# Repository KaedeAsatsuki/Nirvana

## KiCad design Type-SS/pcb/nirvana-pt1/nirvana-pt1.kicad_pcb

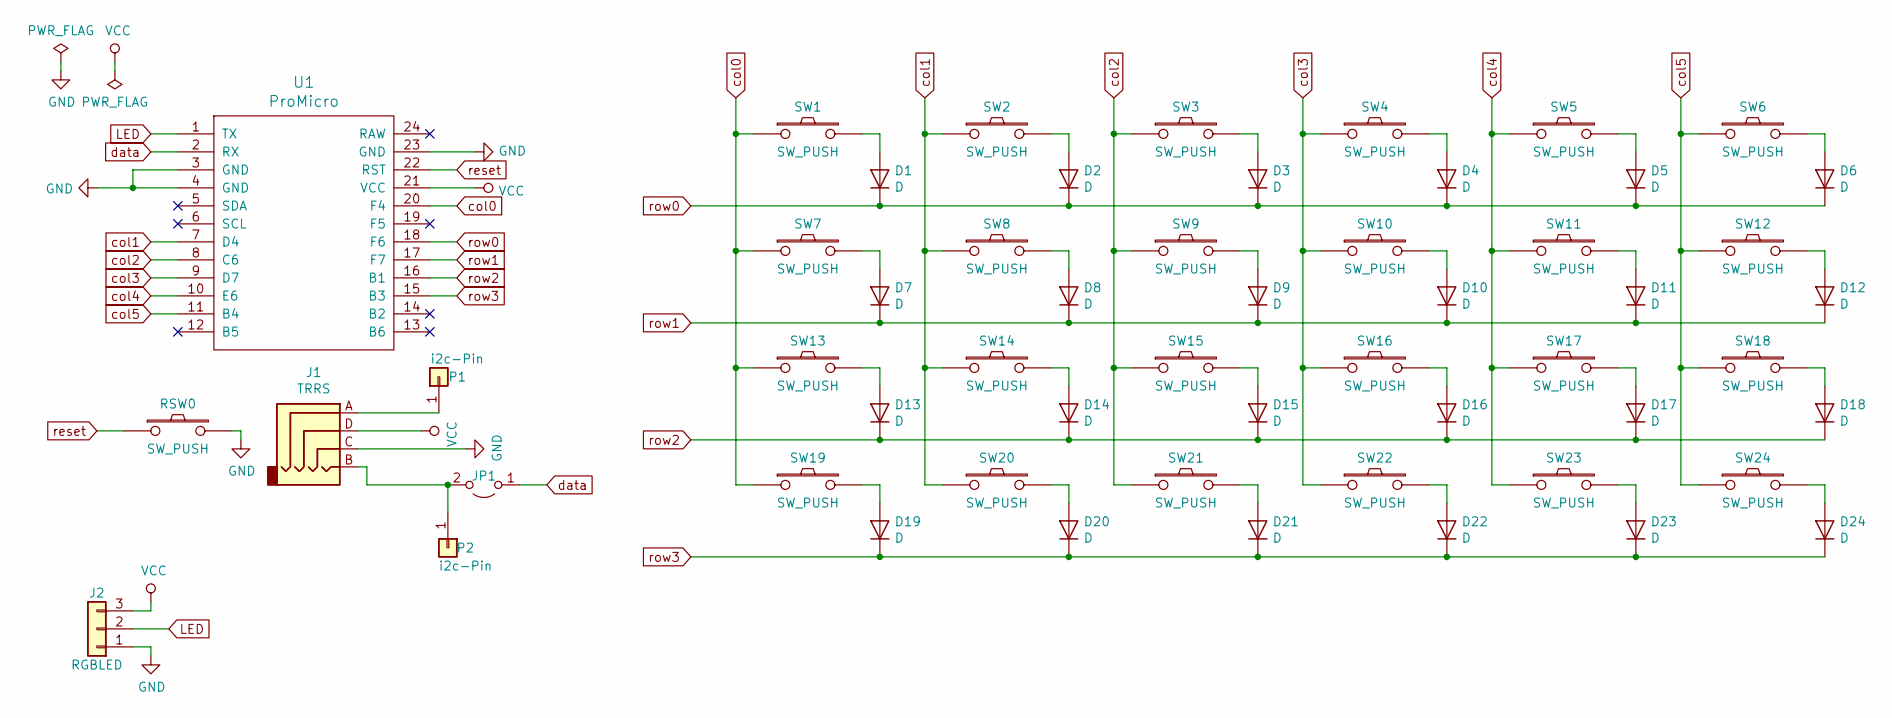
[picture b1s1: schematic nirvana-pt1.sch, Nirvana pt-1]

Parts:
D1, D2, D3, D4, D5, D6, D7, D8, D9, D10, D11, D12, D13, D14, D15, D16, D17, D18, D19, D20, D21, D22, D23, D24: D; D_SMD_re
J1: TRRS; MJ-4PP-9
J2: RGBLED; StripLED_rev
JP1: Jumper_2_Open; SolderJumper-2_P1.3mm_Open_RoundedPad1.0x1.5mm
P1, P2: i2c-Pin; 1pin_conn
RSW0: SW_PUSH; ResetSW
SW1, SW2, SW3, SW4, SW5, SW6, SW7, SW8, SW9, SW10, SW11, SW12, SW13, SW14, SW15, SW16, SW17, SW18, SW21, SW22, SW23, SW24: SW_PUSH; MX_ALPS_PG1350_noLed
SW19, SW20: SW_PUSH; MX_ALPS_PG1350_noLed_1.75u
U1: ProMicro; ProMicro_v2

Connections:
GND: J1.C, J2.1, RSW0.2, U1.3 (GND), U1.4 (GND), U1.23 (GND)
LED: J2.2, U1.1 (TX)
unnamed: D1.2 (A), SW1.2
unnamed: D2.2 (A), SW2.2
unnamed: D3.2 (A), SW3.2
unnamed: D4.2 (A), SW4.2
unnamed: D5.2 (A), SW5.2
unnamed: D6.2 (A), SW6.2
unnamed: D7.2 (A), SW7.2
unnamed: D8.2 (A), SW8.2
unnamed: D9.2 (A), SW9.2
unnamed: D10.2 (A), SW10.2
unnamed: D11.2 (A), SW11.2
unnamed: D12.2 (A), SW12.2
unnamed: D13.2 (A), SW13.2
unnamed: D14.2 (A), SW14.2
unnamed: D15.2 (A), SW15.2
unnamed: D16.2 (A), SW16.2
unnamed: D17.2 (A), SW17.2
unnamed: D18.2 (A), SW18.2
unnamed: D19.2 (A), SW19.2
unnamed: D20.2 (A), SW20.2
unnamed: D21.2 (A), SW21.2
unnamed: D22.2 (A), SW22.2
unnamed: D23.2 (A), SW23.2
unnamed: D24.2 (A), SW24.2
unnamed: J1.A, P1.1
unnamed: J1.B, JP1.2 (B), P2.1
VCC: J1.D, J2.3, U1.21 (VCC)
col0: SW1.1, SW7.1, SW13.1, SW19.1, U1.20 (F4)
col1: SW2.1, SW8.1, SW14.1, SW20.1, U1.7 (D4)
col2: SW3.1, SW9.1, SW15.1, SW21.1, U1.8 (C6)
col3: SW4.1, SW10.1, SW16.1, SW22.1, U1.9 (D7)
col4: SW5.1, SW11.1, SW17.1, SW23.1, U1.10 (E6)
col5: SW6.1, SW12.1, SW18.1, SW24.1, U1.11 (B4)
data: JP1.1 (A), U1.2 (RX)
reset: RSW0.1, U1.22 (RST)
row0: D1.1 (K), D2.1 (K), D3.1 (K), D4.1 (K), D5.1 (K), D6.1 (K), U1.18 (F6)
row1: D7.1 (K), D8.1 (K), D9.1 (K), D10.1 (K), D11.1 (K), D12.1 (K), U1.17 (F7)
row2: D13.1 (K), D14.1 (K), D15.1 (K), D16.1 (K), D17.1 (K), D18.1 (K), U1.16 (B1)
row3: D19.1 (K), D20.1 (K), D21.1 (K), D22.1 (K), D23.1 (K), D24.1 (K), U1.15 (B3)

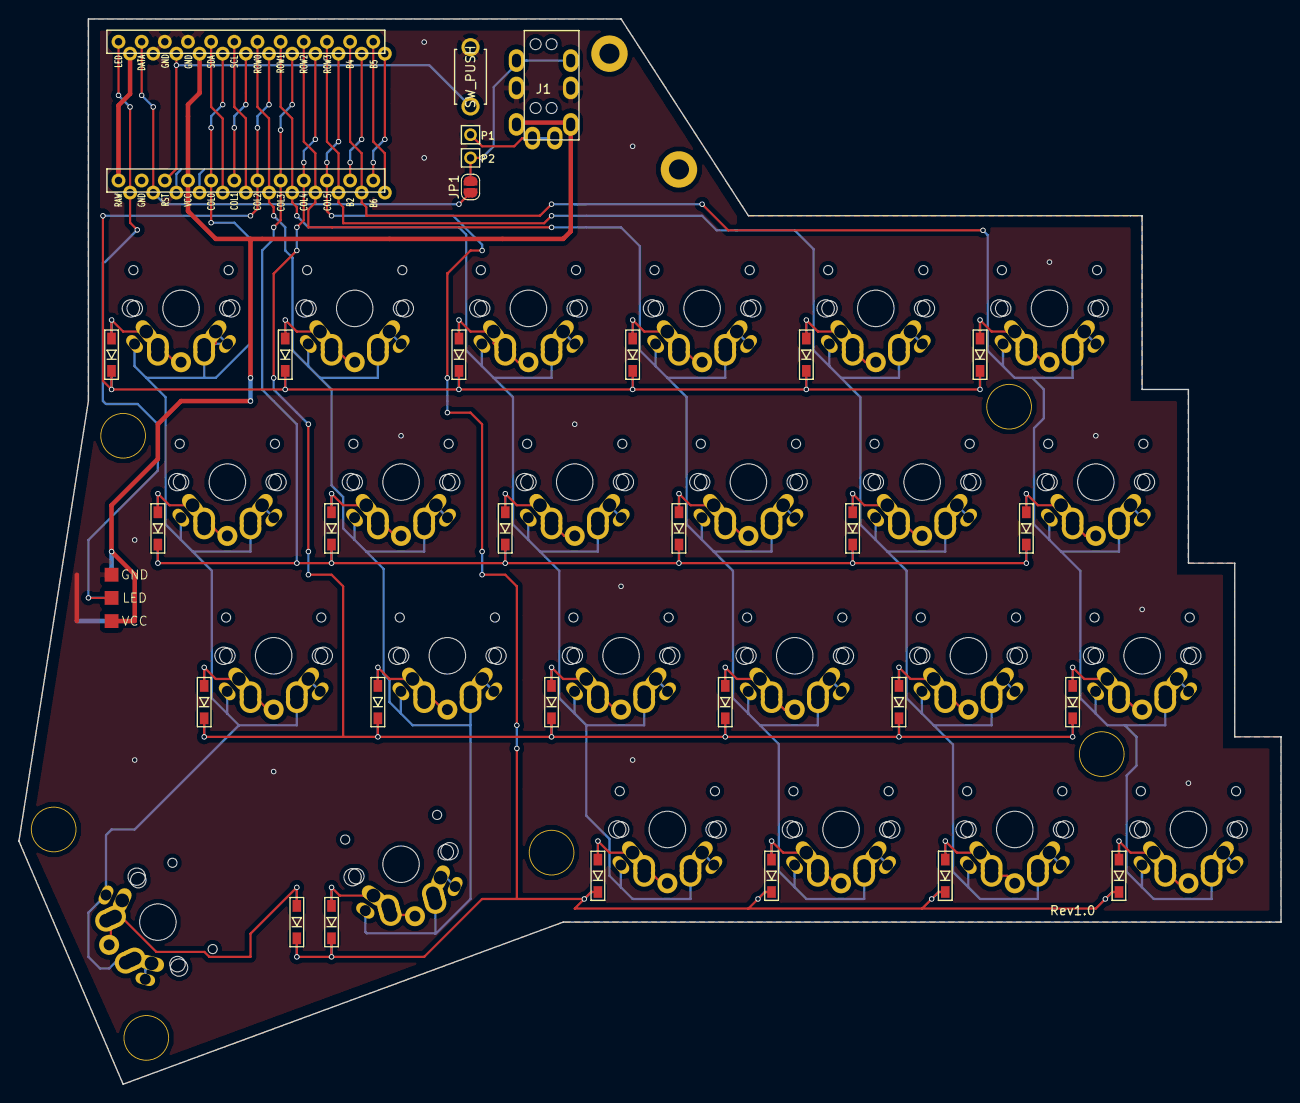
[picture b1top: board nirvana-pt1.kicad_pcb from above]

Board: 2 copper layers, 138.4 x 116.8 mm, 55 parts (0 on the bottom side), 41 nets.

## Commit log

2019-02-01 20190201 first commit
2019-02-03 about TypeSS add
2019-03-01 build guide
2019-03-01 update build

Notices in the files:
Type-SS/pcb/nirvana-pt1/nirvana-pt1.kicad_pcb:
©Kaede Asatsuki
